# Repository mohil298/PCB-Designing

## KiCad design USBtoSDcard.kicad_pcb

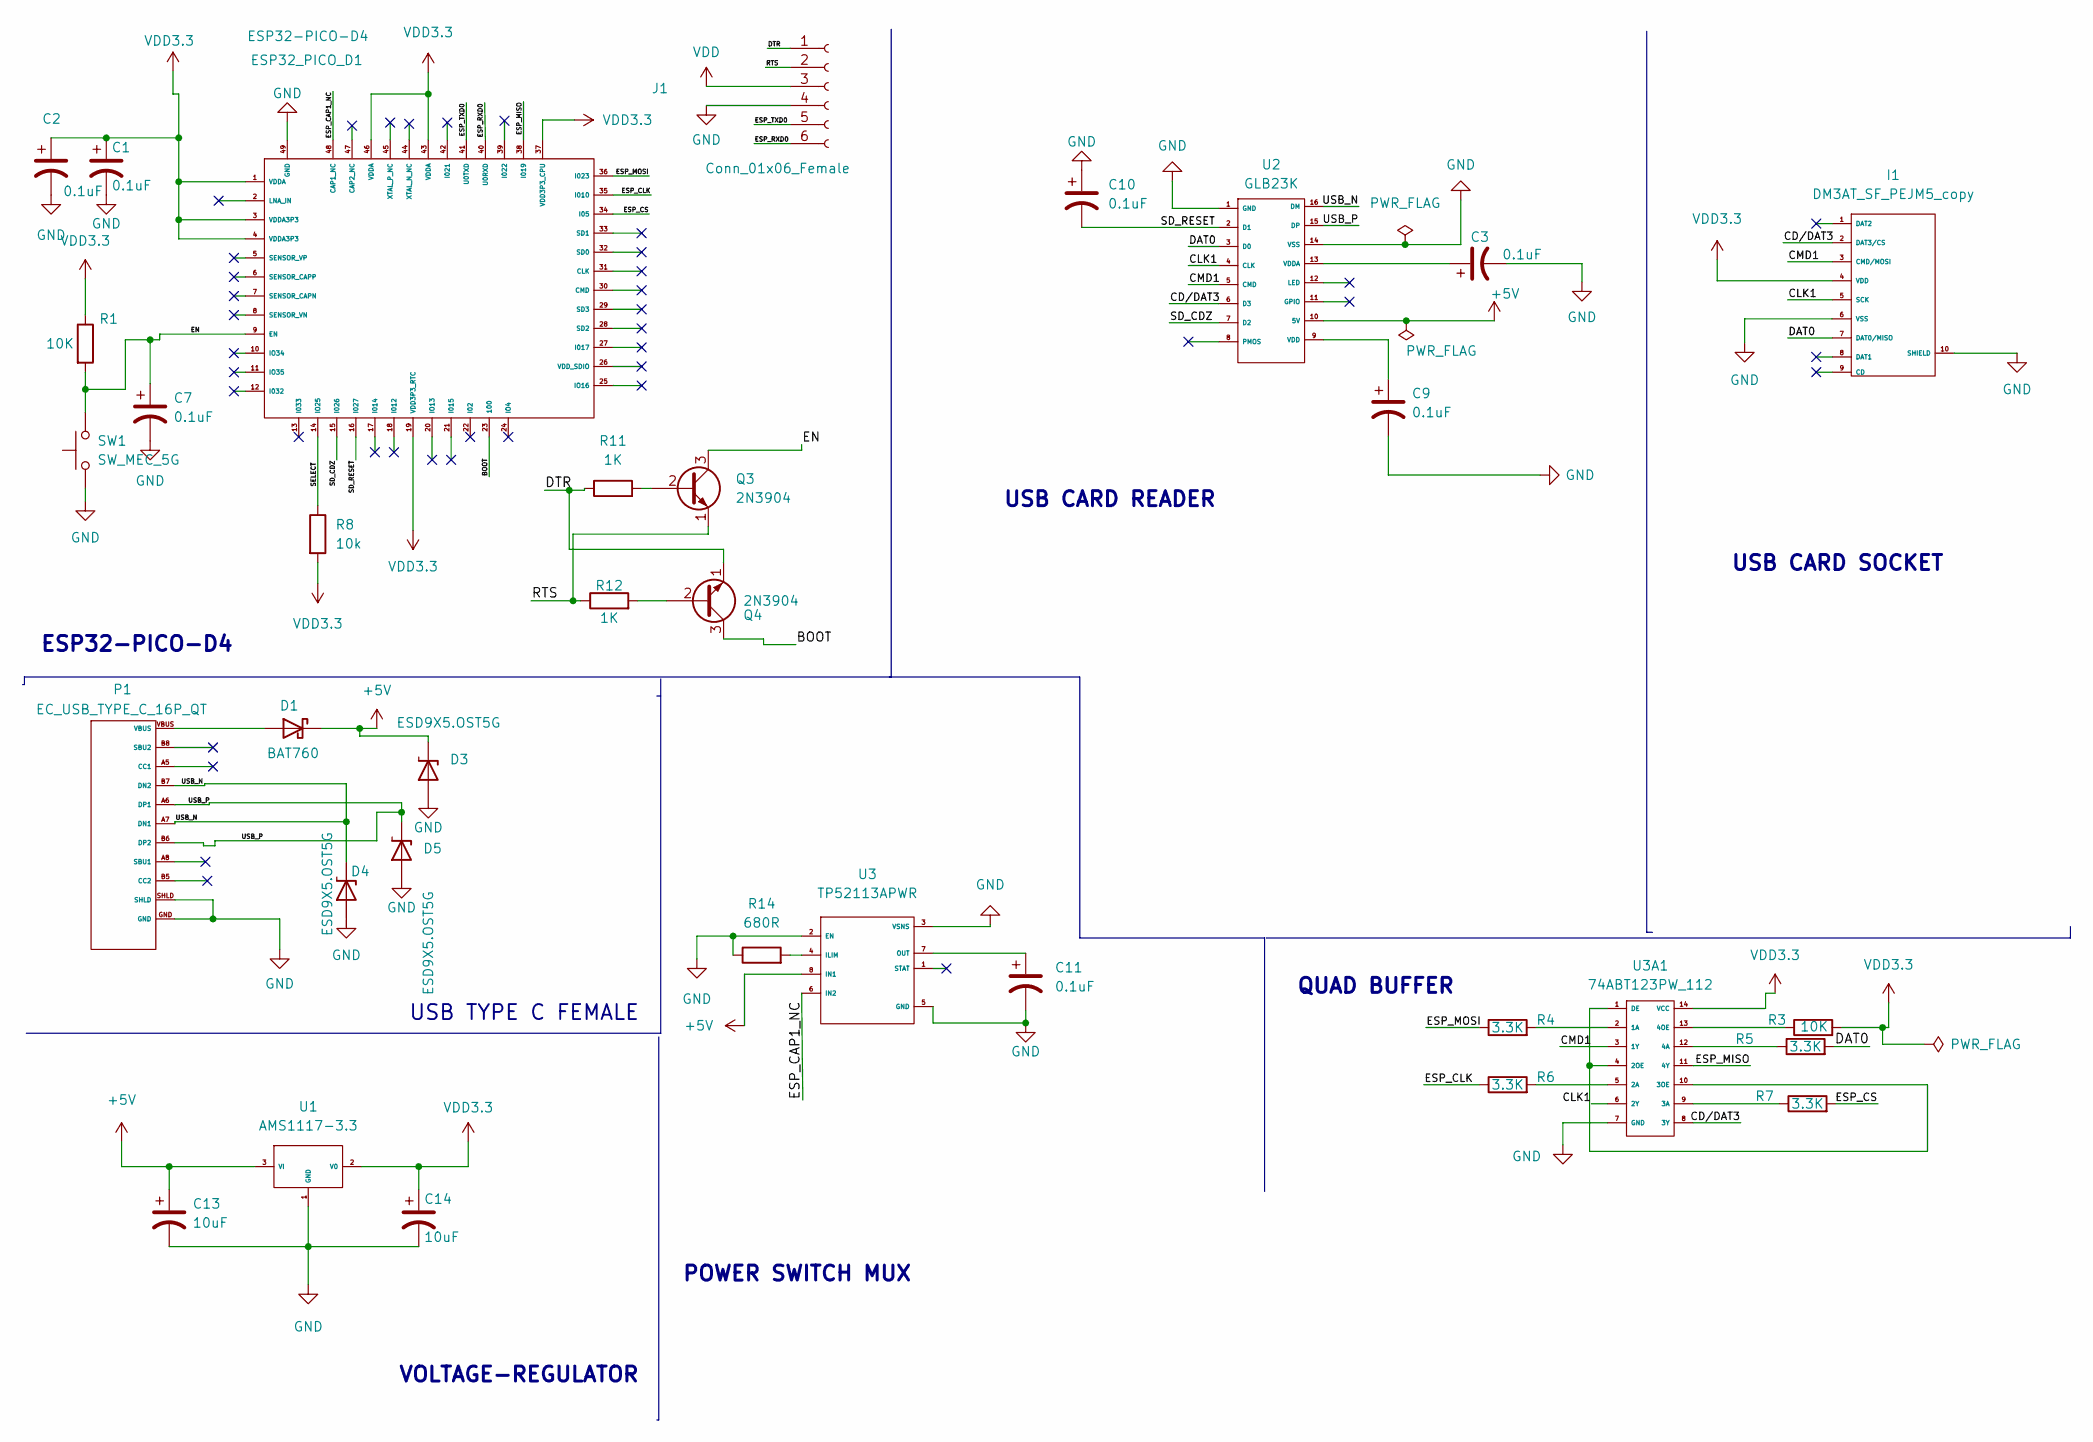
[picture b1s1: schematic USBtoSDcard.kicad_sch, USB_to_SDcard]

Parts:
C1, C2, C3, C7, C9, C10, C11: 0.1uF; C_0603_1608Metric
C13, C14: 10uF; C_0603_1608Metric
D1: BAT760; D_0201_0603Metric
D3, D4, D5: ESD9X5.OST5G; EST
ESP32_PICO_D1: ESP32-PICO-D4; esp32_pico_d4
I1: DM3AT_SF_PEJM5_copy; CARD SOCKET 1
J1: Conn_01x06_Female; CONN_01x06
P1: EC_USB_TYPE_C_16P_QT; USB TYPE C
Q3, Q4: 2N3904; SOT-23
R1, R3: 10K; R_0603_1608Metric
R4, R5, R6, R7: 3.3K; R_0603_1608Metric
R8: 10k; R_0603_1608Metric
R11, R12: 1K; R_0603_1608Metric
R14: 680R; R_0603_1608Metric
SW1: SW_MEC_5G; SW_DIP_SPSTx01_Slide_6.7x4.1mm_W8.61mm_P2.54mm_LowProfile
U1: AMS1117-3.3; VOLTAGE REG 2
U2: GLB23K; gl823k
U3: TP52113APWR; SOP65P640X120-8N
U3A1: 74ABT123PW_112; QUAD BUFFER

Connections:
+5V: C13.1, D1.1 (K), D3.1 (K), U1.3 (VI), U2.10 (5V), U3.8 (IN1)
/BOOT: ESP32_PICO_D1.23 (100), Q4.3 (C)
/CD/DAT3: I1.2 (DAT3/CS), U2.6 (D3), U3A1.8 (3Y)
/CLK1: I1.5 (SCK), U2.4 (CLK), U3A1.6 (2Y)
/CMD1: I1.3 (CMD/MOSI), U2.5 (CMD), U3A1.3 (1Y)
/DAT0: I1.7 (DAT0/MISO), R5.2, U2.3 (D0)
/DTR: J1.1, Q4.1 (E), R11.1
/EN: C7.1, ESP32_PICO_D1.9 (EN), Q3.3 (C), R1.2, SW1.1 (A)
/ESP_CAP1_NC: ESP32_PICO_D1.48 (CAP1_NC), U3.6 (IN2)
/ESP_CLK: ESP32_PICO_D1.35 (I010), R6.1
/ESP_CS: ESP32_PICO_D1.34 (I05), R7.2
/ESP_MISO: ESP32_PICO_D1.38 (I019), U3A1.11 (4Y)
/ESP_MOSI: ESP32_PICO_D1.36 (I023), R4.1
/ESP_RXD0: ESP32_PICO_D1.40 (U0RXD), J1.6
/ESP_TXD0: ESP32_PICO_D1.41 (U0TXD), J1.5
/RTS: J1.2, Q3.1 (E), R12.1
/SD_CDZ: ESP32_PICO_D1.15 (I026), U2.7 (D2)
/SD_RESET: C10.2, ESP32_PICO_D1.16 (I027), U2.2 (D1)
/SELECT: ESP32_PICO_D1.14 (IO25), R8.1
/USB_N: D4.1 (K), P1.A7 (DN1), P1.B7 (DN2), U2.16 (DM)
/USB_P: D5.1 (K), P1.A6 (DP1), P1.B6 (DP2), U2.15 (DP)
GND: C1.2, C2.2, C3.2, C7.2, C9.2, C10.1, C11.2, C13.2, C14.2, D3.2 (A), D4.2 (A), D5.2 (A), ESP32_PICO_D1.49 (GND), I1.6 (VSS), I1.10 (SHIELD), J1.4, P1.GND, P1.SHLD, R14.1, SW1.2 (A), U1.1 (GND), U2.1 (GND), U2.14 (VSS), U3.2 (EN), U3.3 (VSNS), U3.5 (GND), U3A1.7 (GND)
unnamed: C3.1, U2.13 (VDDA)
unnamed: C9.1, U2.9 (VDD)
unnamed: C11.1, U3.7 (OUT)
unnamed: D1.2 (A), P1.VBUS
unnamed: Q3.2 (B), R11.2
unnamed: Q4.2 (B), R12.2
unnamed: R3.1, U3A1.13 (4OE)
unnamed: R4.2, U3A1.2 (1A)
unnamed: R5.1, U3A1.12 (4A)
unnamed: R6.2, U3A1.5 (2A)
unnamed: R7.1, U3A1.9 (3A)
unnamed: R14.2, U3.4 (ILIM)
unnamed: U3A1.1 (DE), U3A1.4 (2OE), U3A1.10 (3OE)

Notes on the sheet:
ESP32-PICO-D4
USB CARD READER
USB CARD SOCKET
POWER SWITCH MUX
USB TYPE C FEMALE
VOLTAGE-REGULATOR
QUAD BUFFER

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
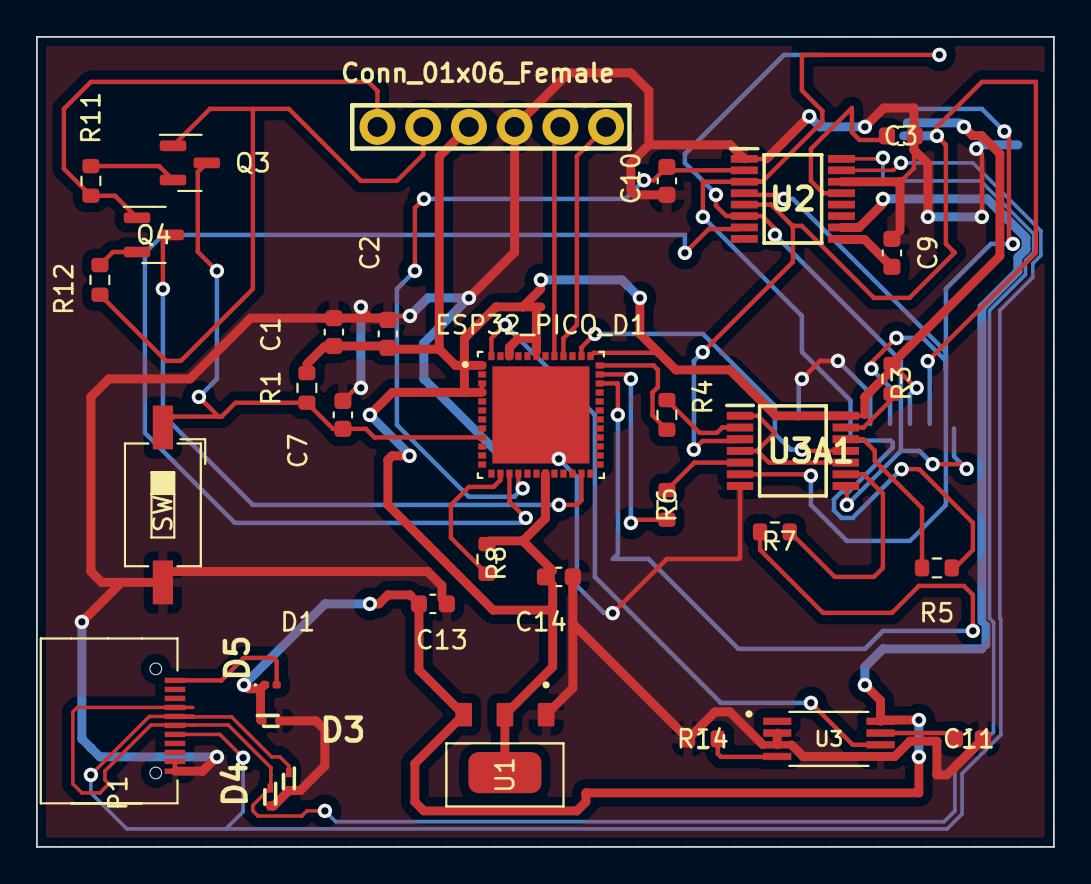
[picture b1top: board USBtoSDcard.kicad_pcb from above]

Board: 2 copper layers, 56.5 x 45.0 mm, 34 parts (1 on the bottom side), 36 nets.
